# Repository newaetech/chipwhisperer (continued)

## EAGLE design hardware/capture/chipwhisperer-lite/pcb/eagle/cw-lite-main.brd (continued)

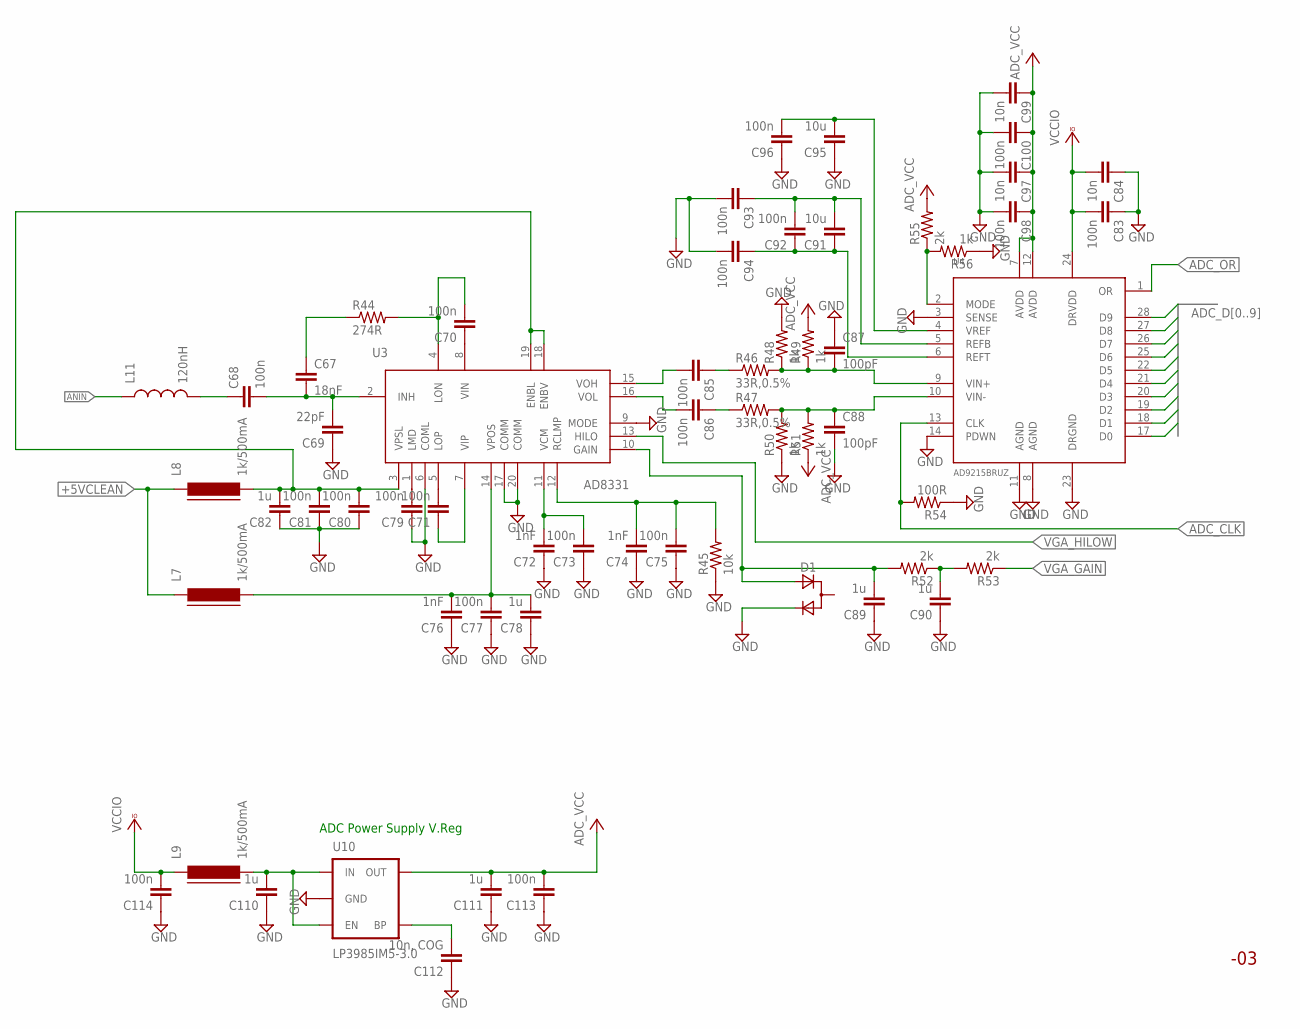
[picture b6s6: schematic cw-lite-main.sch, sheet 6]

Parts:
C67: 18nF; 0603C
C68, C85, C86: 100n; 0603C
C69: 22pF; 0603C
C70, C71, C73, C75, C77, C79, C80, C81, C83, C92, C93, C94, C96, C98, C100, C113, C114: 100n; 0402C
C72, C74, C76: 1nF; 0402C
C78, C82, C89, C90, C110, C111: 1u; 0603C
C84, C97, C99: 10n; 0402C
C87, C88: 100pF; 0603C
C91, C95: 10u; 0603C
C112: 10n, COG; 0402C
D1: D_ACACSOT23; SOT-23; MPN BAV99-7F
L7, L8, L9: 1k/500mA; FB603
L11: 120nH; 0603
R44: 274R; 0603R
R45: 10k; 0603R
R46, R47: 33R,0.5%; 0603R
R48, R49, R50, R51: 1k; 0402R
R52, R53, R55: 2k; 0603R
R54: 100R; 0603R
R56: 1k; 0603R
U3: AD8331; QSOP20; MPN AD8331ARQZ
U4: AD9215BRUZ; TSSOP28; MPN AD9215BRUZ-105
U10: LP3985IM5-3.0; SOT23-5; MPN LP3985IM5X-3.0/NOPB

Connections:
+5VCLEAN: L7.1, L8.1; also elsewhere on the board
ADC_CLK: R54.2, U4.13 (CLK); also elsewhere on the board
ADC_D0: U4.17 (D0); also elsewhere on the board
ADC_D1: U4.18 (D1); also elsewhere on the board
ADC_D2: U4.19 (D2); also elsewhere on the board
ADC_D3: U4.20 (D3); also elsewhere on the board
ADC_D4: U4.21 (D4); also elsewhere on the board
ADC_D5: U4.22 (D5); also elsewhere on the board
ADC_D6: U4.25 (D6); also elsewhere on the board
ADC_D7: U4.26 (D7); also elsewhere on the board
ADC_D8: U4.27 (D8); also elsewhere on the board
ADC_D9: U4.28 (D9); also elsewhere on the board
ADC_OR: U4.1 (OR); also elsewhere on the board
ADC_VCC: C97.1, C98.1, C99.1, C100.1, C111.2, C113.2, R49.2, R51.1, R55.2, U4.7 (AVDD), U4.12 (AVDD), U10.5 (OUT)
ANIN: L11.1; also elsewhere on the board
GND: C69.1, C72.1, C73.1, C74.1, C75.1, C76.1, C77.1, C78.1, C79.1, C80.1, C81.1, C82.1, C83.1, C84.1, C87.1, C88.2, C89.1, C90.1, C93.2, C94.2, C95.1, C96.1, C97.2, C98.2, C99.2, C100.2, C110.1, C111.1, C112.1, C113.1, C114.1, D1.2 (C), R45.1, R48.2, R50.1, R54.1, R56.1, U3.6 (COML), U3.9 (MODE), U3.17 (COMM), U3.20 (COMM), U4.3 (SENSE), U4.8 (AGND), U4.11 (AGND), U4.14 (PDWN), U4.23 (DRGND), U10.2 (GND); also elsewhere on the board
unnamed: C68.1, L11.2
unnamed: C110.2, L9.2, U10.1 (IN), U10.3 (EN)
unnamed: C112.2, U10.4 (BP)
unnamed: C67.2, C68.2, C69.2, U3.2 (INH)
unnamed: C70.2, R44.2, U3.4 (LON)
unnamed: C67.1, R44.1
unnamed: C70.1, U3.8 (VIN)
unnamed: C71.2, U3.5 (LOP)
unnamed: C74.2, C75.2, R45.2, U3.12 (RCLMP)
unnamed: C72.2, C73.2, U3.11 (VCM)
unnamed: C79.2, U3.1 (LMD)
unnamed: C89.2, D1.3 (A), R52.2, U3.10 (GAIN)
unnamed: C80.2, C81.2, C82.2, L8.2, U3.3 (VPSL), U3.18 (ENBV), U3.19 (ENBL)
unnamed: C71.1, U3.7 (VIP)
unnamed: C76.2, C77.2, C78.2, L7.2, U3.14 (VPOS)
unnamed: C87.2, R46.2, R48.1, R49.1, U4.9 (VIN+)
unnamed: C88.1, R47.2, R50.2, R51.2, U4.10 (VIN-)
unnamed: C85.2, U3.15 (VOH)
unnamed: C86.2, U3.16 (VOL)
unnamed: C85.1, R46.1
unnamed: C86.1, R47.1
unnamed: C91.2, C92.2, C93.1, U4.5 (REFB)
unnamed: C91.1, C92.1, C94.1, U4.6 (REFT)
unnamed: C90.2, R52.1, R53.2
unnamed: C95.2, C96.2, U4.4 (VREF)
unnamed: R55.1, R56.2, U4.2 (MODE)
VCCIO: C83.2, C84.2, C114.2, L9.1, U4.24 (DRVDD); also elsewhere on the board
VGA_GAIN: R53.1; also elsewhere on the board
VGA_HILOW: U3.13 (HILO); also elsewhere on the board

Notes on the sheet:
ADC Power Supply V.Reg

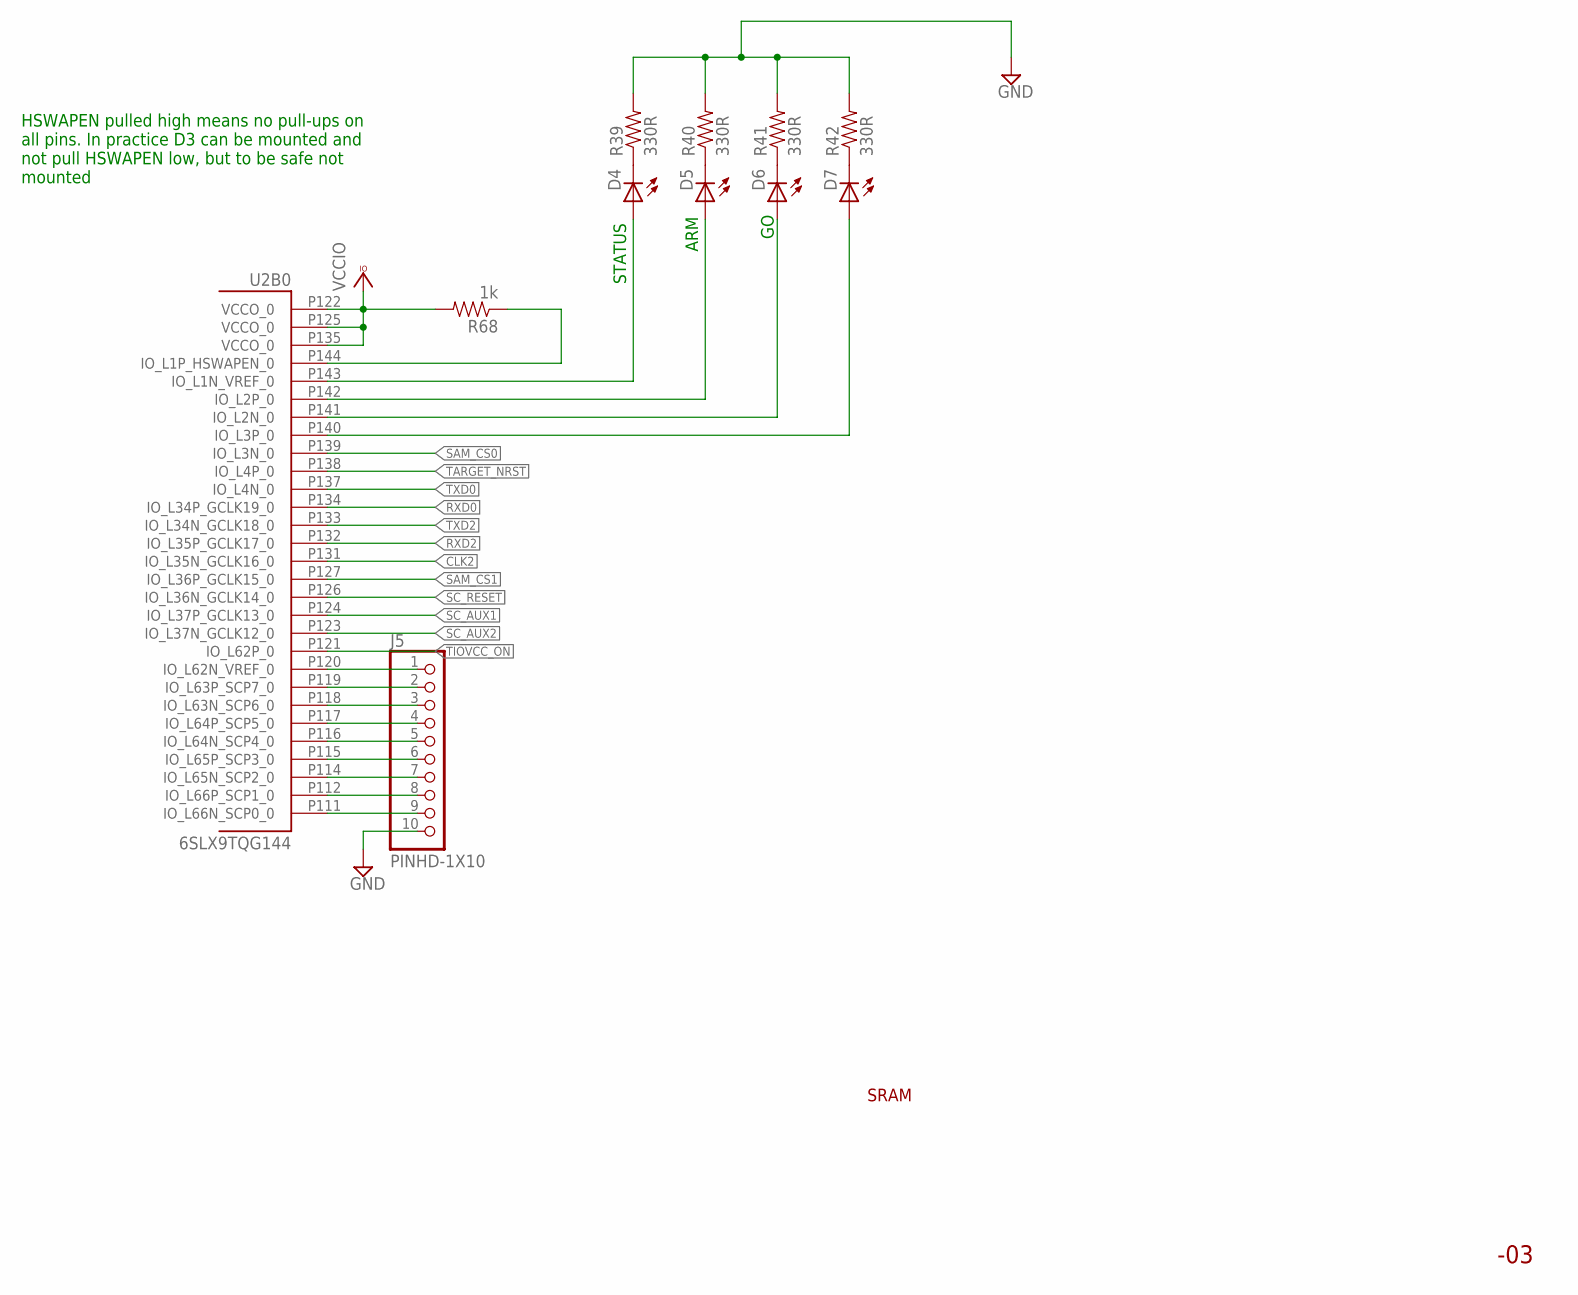
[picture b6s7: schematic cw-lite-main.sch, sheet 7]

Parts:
D4, D5, D6, D7: LED0603; LED-0603
J5: PINHD-1X10; 1X10-BIG
R39, R40, R41, R42: 330R; 0402R
R68: 1k; 0402R
U2: 6SLX9TQG144; TQ144; MPN XC6SLX9-3TQG144C

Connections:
!TIOVCC_ON: U2.P121 (IO_L62P_0); also elsewhere on the board
CLK2: U2.P131 (IO_L35N_GCLK16_0); also elsewhere on the board
GND: J5.10, R39.2, R40.2, R41.2, R42.2; also elsewhere on the board
LED_ARMED: D6.A, U2.P141 (IO_L2N_0)
LED_CAPTURE: D5.A, U2.P142 (IO_L2P_0)
LED_STATUS: R68.1, U2.P144 (IO_L1P_HSWAPEN_0)
LED_TCLOCK: D7.A, U2.P140 (IO_L3P_0)
LED_USBACT: D4.A, U2.P143 (IO_L1N_VREF_0)
unnamed: J5.1, U2.P120 (IO_L62N_VREF_0)
unnamed: J5.2, U2.P119 (IO_L63P_SCP7_0)
unnamed: J5.3, U2.P118 (IO_L63N_SCP6_0)
unnamed: J5.4, U2.P117 (IO_L64P_SCP5_0)
unnamed: J5.5, U2.P116 (IO_L64N_SCP4_0)
unnamed: J5.6, U2.P115 (IO_L65P_SCP3_0)
unnamed: J5.7, U2.P114 (IO_L65N_SCP2_0)
unnamed: J5.8, U2.P112 (IO_L66P_SCP1_0)
unnamed: J5.9, U2.P111 (IO_L66N_SCP0_0)
unnamed: D4.C, R39.1
unnamed: D5.C, R40.1
unnamed: D6.C, R41.1
unnamed: D7.C, R42.1
RXD0: U2.P134 (IO_L34P_GCLK19_0); also elsewhere on the board
RXD2: U2.P132 (IO_L35P_GCLK17_0); also elsewhere on the board
SAM_CS0: U2.P139 (IO_L3N_0); also elsewhere on the board
SAM_CS1: U2.P127 (IO_L36P_GCLK15_0); also elsewhere on the board
SC_AUX1: U2.P124 (IO_L37P_GCLK13_0); also elsewhere on the board
SC_AUX2: U2.P123 (IO_L37N_GCLK12_0); also elsewhere on the board
SC_RESET: U2.P126 (IO_L36N_GCLK14_0); also elsewhere on the board
TARGET_NRST: U2.P138 (IO_L4P_0); also elsewhere on the board
TXD0: U2.P137 (IO_L4N_0); also elsewhere on the board
TXD2: U2.P133 (IO_L34N_GCLK18_0); also elsewhere on the board
VCCIO: R68.2, U2.P122 (VCCO_0), U2.P125 (VCCO_0), U2.P135 (VCCO_0); also elsewhere on the board

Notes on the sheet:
SRAM
HSWAPEN pulled high means no pull-ups on all pins. In practice D3 can be mounted and not pull HSWAPEN low, but to be safe not mounted
STATUS
ARM

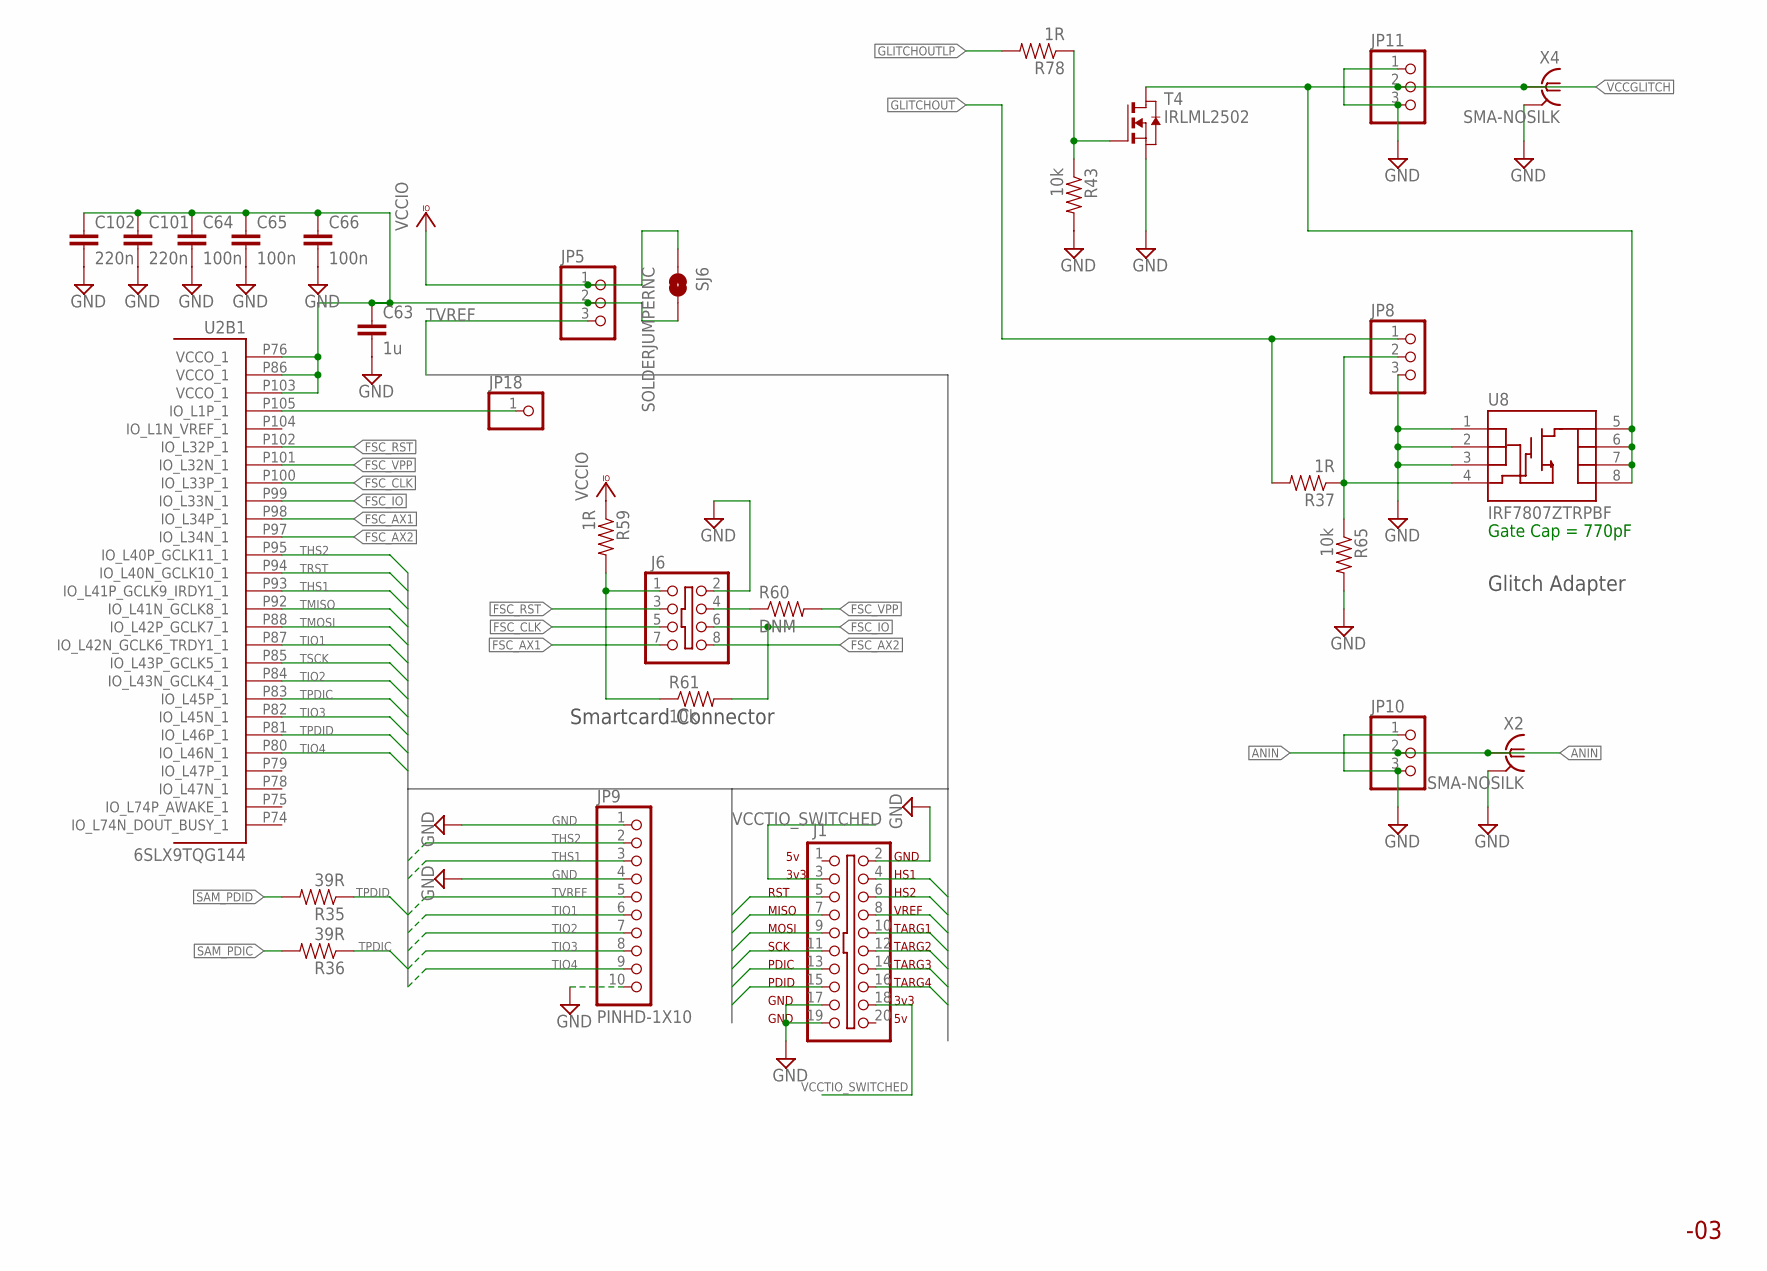
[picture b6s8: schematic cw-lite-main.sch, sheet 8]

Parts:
C63: 1u; 0603C
C64, C65, C66: 100n; 0402C
C101, C102: 220n; 0402C
J1: SHROUD_2X10-SHROUDED; PINSHRD_PTH_2X10
J6: SHROUD_2X4SHROUD; PINSHRD_PTH_2X04
JP5, JP8, JP10, JP11: PINHD-1X3; 1X03
JP9: PINHD-1X10; 1X10-BIG
JP18: PINHD-1X1; 1X01
R35, R36: 39R; 0603R
R37, R59, R78: 1R; 0603R
R43, R61, R65: 10k; 0603R
R60: DNM; 0603R
SJ6: SOLDERJUMPERNC; SJ_2S
T4: IRLML2502; SOT-23; MPN IRLML2502TRPBF
U2: 6SLX9TQG144; TQ144; MPN XC6SLX9-3TQG144C
U8: IRF7807ZTRPBF; SO08
X2, X4: SMA-NOSILK; J502-ND-142-0711-821/826-NOSILK

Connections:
ANIN: JP10.2, X2.1; also elsewhere on the board
FSC_AX1: J6.7, U2.P98 (IO_L34P_1)
FSC_AX2: J6.8, U2.P97 (IO_L34N_1)
FSC_CLK: J6.5, U2.P100 (IO_L33P_1)
FSC_IO: J6.6, R61.2, U2.P99 (IO_L33N_1)
FSC_RST: J6.3, U2.P102 (IO_L32P_1)
FSC_VPP: R60.2, U2.P101 (IO_L32N_1)
GLITCHOUT: JP8.1, R37.2; also elsewhere on the board
GLITCHOUTLP: R78.2; also elsewhere on the board
GND: C63.2, C64.2, C65.2, C66.2, C101.2, C102.2, J1.2, J1.17, J1.19, J6.2, JP8.3, JP9.1, JP9.4, JP9.10, JP10.1, JP10.3, JP11.1, JP11.3, R43.2, R65.2, T4.2 (S), U8.1 (S), U8.2 (S), U8.3 (S), X2.G@1 (2), X2.G@2 (2), X2.G@3 (2), X2.G@4 (2), X4.G@1 (2), X4.G@2 (2), X4.G@3 (2), X4.G@4 (2); also elsewhere on the board
unnamed: JP8.2, R37.1, R65.1, U8.4 (G)
unnamed: JP18.1, U2.P105 (IO_L1P_1)
unnamed: R43.1, R78.1, T4.3 (G)
unnamed: J6.1, R59.2, R61.1
unnamed: J6.4, R60.1
SAM_PDIC: R36.2; also elsewhere on the board
SAM_PDID: R35.2; also elsewhere on the board
TARGET_VCCIO: C63.1, C64.1, C65.1, C66.1, C101.1, C102.1, JP5.2, SJ6.2, U2.P76 (VCCO_1), U2.P86 (VCCO_1), U2.P103 (VCCO_1)
THS1: J1.4, JP9.3, U2.P93 (IO_L41P_GCLK9_IRDY1_1); also elsewhere on the board
THS2: J1.6, JP9.2, U2.P95 (IO_L40P_GCLK11_1); also elsewhere on the board
TIO1: J1.10, JP9.6, U2.P87 (IO_L42N_GCLK6_TRDY1_1); also elsewhere on the board
TIO2: J1.12, JP9.7, U2.P84 (IO_L43N_GCLK4_1); also elsewhere on the board
TIO3: J1.14, JP9.8, U2.P82 (IO_L45N_1); also elsewhere on the board
TIO4: J1.16, JP9.9, U2.P80 (IO_L46N_1); also elsewhere on the board
TMISO: J1.7, U2.P92 (IO_L41N_GCLK8_1); also elsewhere on the board
TMOSI: J1.9, U2.P88 (IO_L42P_GCLK7_1); also elsewhere on the board
TPDIC: J1.13, R36.1, U2.P83 (IO_L45P_1); also elsewhere on the board
TPDID: J1.15, R35.1, U2.P81 (IO_L46P_1); also elsewhere on the board
TRST: J1.5, U2.P94 (IO_L40N_GCLK10_1); also elsewhere on the board
TSCK: J1.11, U2.P85 (IO_L43P_GCLK5_1); also elsewhere on the board
TVREF: J1.8, JP5.3, JP9.5; also elsewhere on the board
VCCGLITCH: JP11.2, T4.1 (D), U8.5 (D), U8.6 (D), U8.7 (D), U8.8 (D), X4.1; also elsewhere on the board
VCCIO: JP5.1, R59.1, SJ6.1; also elsewhere on the board
VCCTIO_SWITCHED: J1.3, J1.18; also elsewhere on the board

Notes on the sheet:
HS1
HS2
VREF
TARG1
TARG2
TARG3
TARG4
3v3
RST
MISO
MOSI
SCK
PDIC
PDID
GND
Glitch Adapter
Smartcard Connector
Gate Cap = 770pF

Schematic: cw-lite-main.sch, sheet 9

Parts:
C37: 47u; 0805
C103: 10u; 0603C
C104: 10n; 0603C
C105, C107: 1u; 0603C
C106, C108, C109: 100n; 0603C
C115, C116, C121: DNM; 0603C
C118, C119, C120: CAP0603-CAP; 0603C
J2: SHROUD_2X10-SHROUDED; PINSHRD_PTH_2X10
J9: MICRO-USB-5P-ZX62D-B-5P8; B-SMD-5P-TH
JP6, JP7, JP12: PINHD-1X2; 1X02
JP13: PINHD-1X9; 1X09-BIG
JP14, JP15, JP16, JP17: PINHD-1X1; 1X01
L10: 1k/500mA; FB603
LED9, LED10: LED-0603; LED-603
Q2: CRYSTALHC49U-V; HC49U-V
R13: 10k; 0603R
R66, R76: 49R9; 0805
R67, R72: 100R; 0603R
R73: DNM; 0603R
R74, R75: 1k; 0603R
SJ2: SOLDERJUMPER_2WAYPASTE2&3; SJ_3_PASTE2&3
SJ3, SJ4, SJ5, SJ7: SOLDERJUMPERNC; SJ_2S
U11: V_REG_MIC2920; SOT223
U12: XMEGA128A4U; TQFP44; MPN ATXMEGA128A4U-AU
X3, X5: SMA-NOSILK; J502-ND-142-0711-821/826-NOSILK

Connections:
ANIN: JP7.2, SJ4.2, X3.1; also elsewhere on the board
GND: C37.2, C103.2, C104.2, C105.2, C106.2, C107.2, C108.2, C109.1, C115.2, C116.1, C118.1, C119.1, C120.1, C121.1, J2.2, J2.17, J2.19, J9.5 (GND), JP13.9, U11.2 (GND), U12.8 (GND), U12.18 (GND1), U12.30 (GND2), U12.38 (GND3), X3.G@1 (2), X3.G@2 (2), X3.G@3 (2), X3.G@4 (2), X5.G@1 (2), X5.G@2 (2), X5.G@3 (2), X5.G@4 (2); also elsewhere on the board
unnamed: C118.2, J9.E1 (SHIELD), J9.E2 (SHIELD), J9.P$1 (SHIELD), J9.P$2 (SHIELD), J9.P$3 (SHIELD), J9.P$4 (SHIELD)
unnamed: C107.1, C108.1, C109.2, JP12.1, R66.2, SJ3.2, U12.39 (AVCC)
unnamed: C121.2, JP6.1, JP7.1, R66.1, SJ4.1, SJ5.1, U12.9 (VCC), U12.19 (VCC1), U12.31 (VCC2)
unnamed: C119.2, J9.1 (VCC), U11.1 (IN)
unnamed: C120.2, SJ2.1, U11.3 (OUT)
unnamed: LED9.A, R74.1
unnamed: LED10.A, R75.1
unnamed: LED9.C, U12.1 (PA5)
unnamed: LED10.C, U12.2 (PA6)
unnamed: JP13.1, U12.25 (PD5)
unnamed: JP13.2, U12.24 (PD4)
unnamed: JP13.3, U12.23 (PD3)
unnamed: JP13.4, U12.22 (PD2)
unnamed: JP13.5, U12.21 (PD1)
unnamed: C115.1, Q2.2, R72.1, U12.37 (PR1(XT1))
unnamed: C116.2, Q2.1, R73.1, U12.36 (PR0(XT2))
unnamed: R67.2, U12.7 (PB3)
unnamed: JP13.6, U12.20 (PD0)
unnamed: L10.2, R76.2
unnamed: C37.1, C105.1, C106.1, JP12.2, R76.1, SJ3.1
THS1: J2.4, R67.1; also elsewhere on the board
THS2: J2.6, R72.2, R73.2; also elsewhere on the board
TIO1: J2.10, JP16.1, U12.13 (PC3); also elsewhere on the board
TIO2: J2.12, JP17.1, U12.12 (PC2); also elsewhere on the board
TIO3: J2.14, JP14.1, U12.41 (PA1); also elsewhere on the board
TIO4: J2.16, JP15.1, U12.40 (PA0); also elsewhere on the board
TMISO: J2.7; also elsewhere on the board
TMOSI: J2.9; also elsewhere on the board
TPC6: JP13.8, U12.16 (PC6)
TPC7: JP13.7, U12.17 (PC7)
TPDIC: J2.13, R13.2, U12.35 (!RESET!/PDI_CLK); also elsewhere on the board
TPDID: J2.15, U12.34 (PDI_DATA); also elsewhere on the board
TRST: J2.5; also elsewhere on the board
TSCK: J2.11; also elsewhere on the board
TUSB_N: J9.2 (DM), U12.26 (PD6)
TUSB_P: J9.3 (DP), U12.27 (PD7)
TVREF: J2.8, SJ7.2; also elsewhere on the board
VCCGLITCH: JP6.2, SJ5.2, X5.1; also elsewhere on the board
VCCTIO_SWITCHED: J2.3, J2.18, SJ2.3; also elsewhere on the board
VCC_TARG: C103.1, C104.1, L10.1, R13.1, R74.2, R75.2, SJ2.2, SJ7.1

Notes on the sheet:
Breakaway Section of PCB
Might be XMEGA128D3 instead?

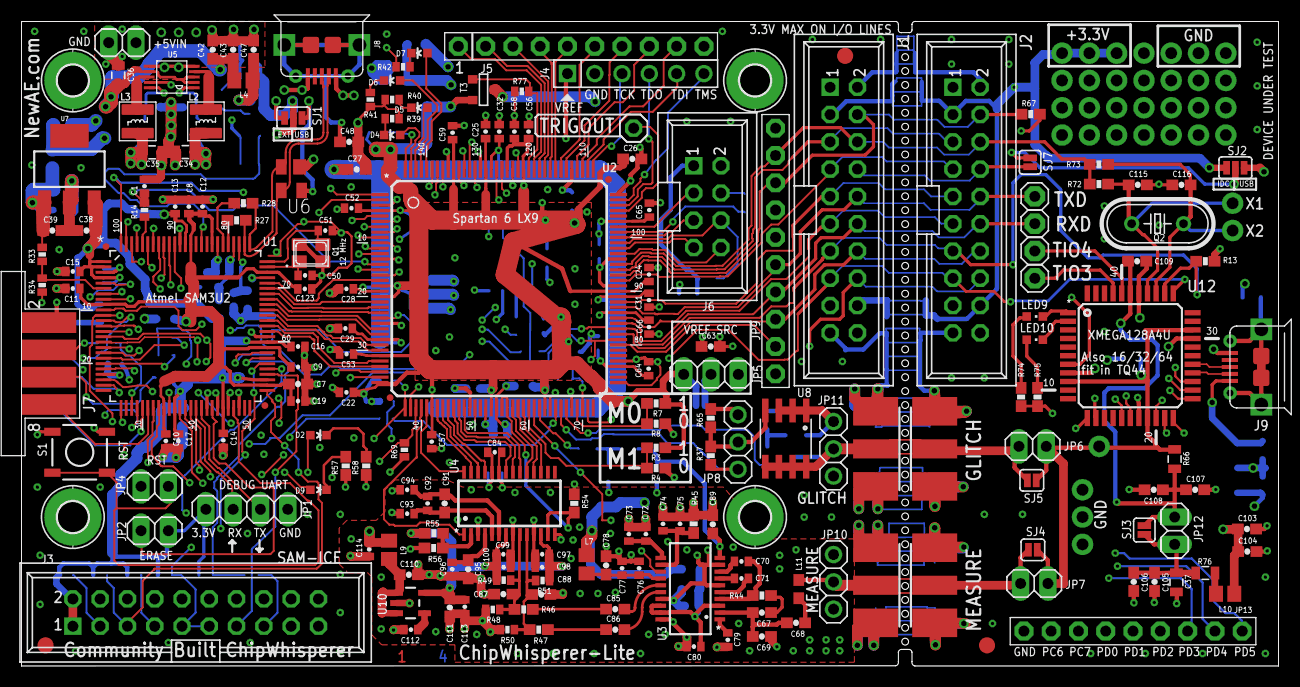
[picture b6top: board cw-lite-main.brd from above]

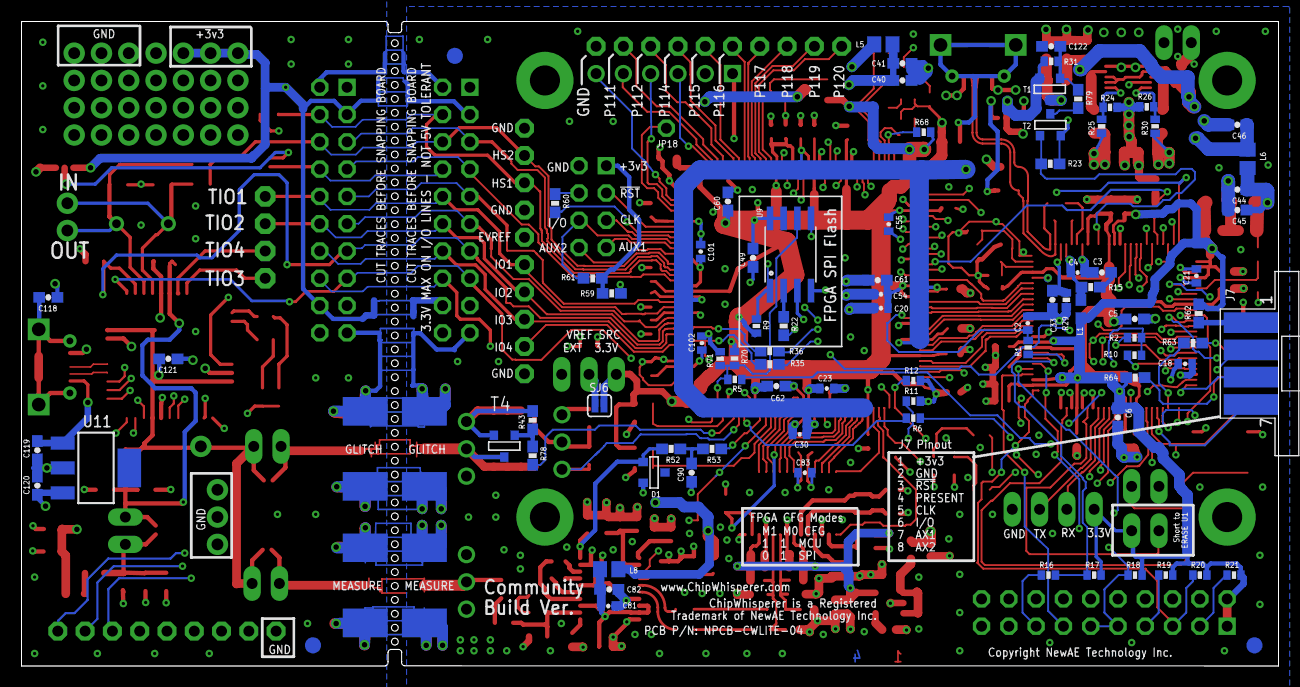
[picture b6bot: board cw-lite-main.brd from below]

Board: 4 copper layers, 117.0 x 60.0 mm, 290 parts (86 on the bottom side), 223 nets.

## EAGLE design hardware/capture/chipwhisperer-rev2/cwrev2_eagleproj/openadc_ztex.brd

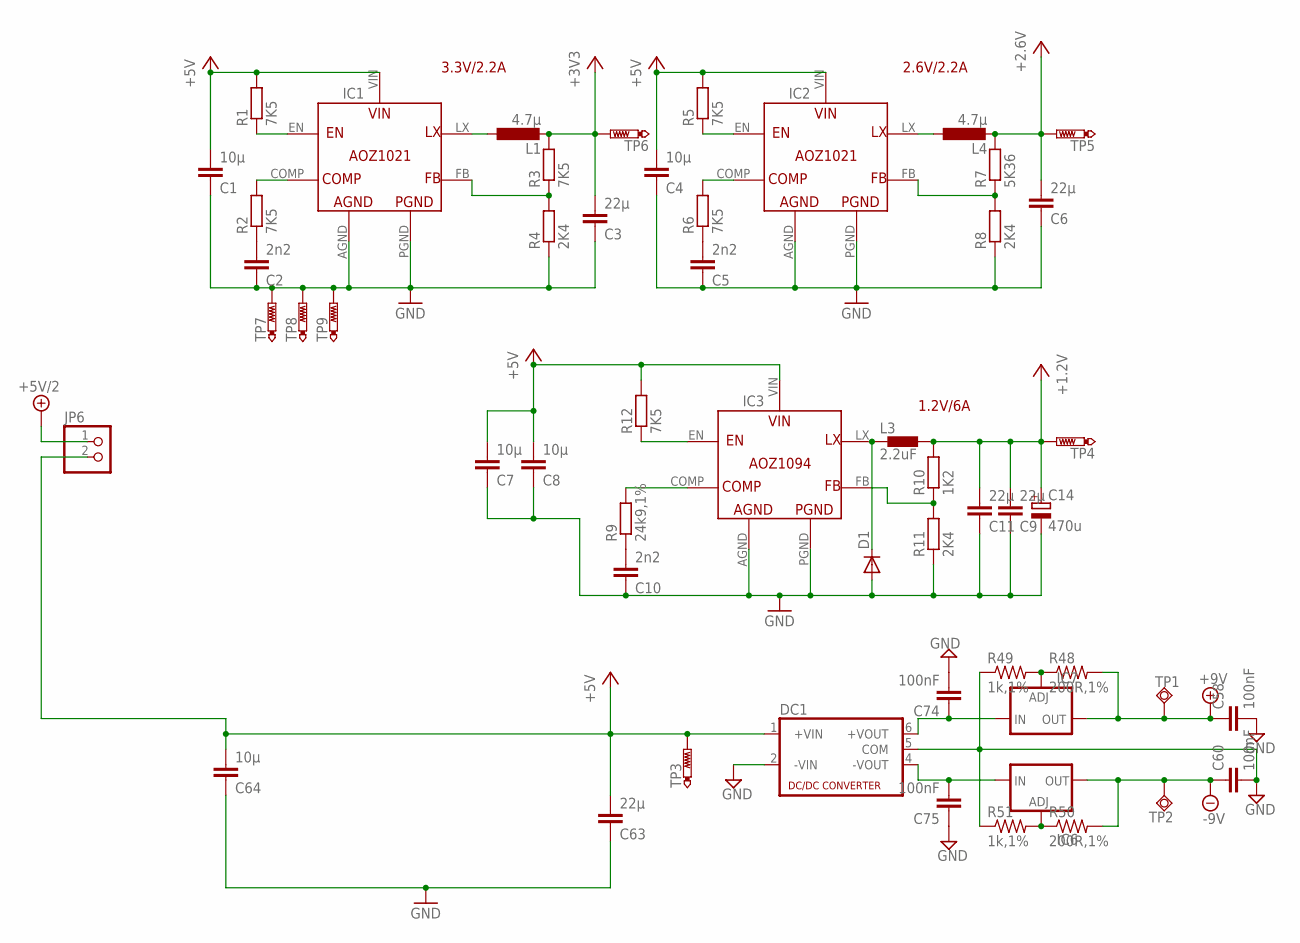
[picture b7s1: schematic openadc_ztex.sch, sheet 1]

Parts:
C1, C4, C7, C8, C64: 10µ; C1206
C2, C5, C10: 2n2; C0805K
C3, C6, C9, C11, C63: 22µ; C0805K
C14: 470u; E2,5-6
C58, C60, C74, C75: 100nF; C0603
D1: DIODE-MELF-MLL41; MELF-MLL41
DC1: NMA
IC1, IC2: AOZ1021
IC3: AOZ1094; AOZ1094.PAC
IC6: LM337L; 337L
IC7: LM317L; 317L
JP6: PINHD-1X2; 1X02
L1, L4: 4.7µ; NR60; DIGIKEY# 587-2100-1-ND
L3: 2.2uF; DR1030MOD.PAC; MPN CDRH104RNP-2R5NC
R1, R2, R3, R5, R6, R12: 7K5; R0805K
R4, R8, R11: 2K4; R0805K
R7: 5K36; R0805K
R9: 24k9,1%; R0805K
R10: 1K2; R0805K
R48, R50: 200R,1%; R0603
R49, R51: 1k,1%; R0603
TP1, TP2: TPSQPAD1-13; P1-13
TP3, TP4, TP5, TP6, TP7, TP8, TP9: PTR1PAD1-13; P1-13

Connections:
+1.2V: C9.2, C11.2, C14.+, L3.2, R10.2, TP4.TP; also elsewhere on the board
+2.6V: C6.2, L4.P$2 (2), R7.2, TP5.TP; also elsewhere on the board
+3V3: C3.2, L1.P$2 (2), R3.2, TP6.TP; also elsewhere on the board
+5V: C1.2, C4.2, C7.2, C8.2, C63.2, C64.2, DC1.1 (+VIN), IC1.VIN, IC2.VIN, IC3.VIN, JP6.2, R1.2, R5.2, R12.2, TP3.TP; also elsewhere on the board
+5V/2: JP6.1; also elsewhere on the board
+9V: C58.1, IC7.2 (OUT), R48.2, TP1.TP; also elsewhere on the board
-9V: C60.1, IC6.OUT, R50.2, TP2.TP; also elsewhere on the board
GND: C1.1, C2.1, C3.1, C4.1, C5.1, C6.1, C7.1, C8.1, C9.1, C10.1, C11.1, C14.-, C58.2, C60.2, C63.1, C64.1, C74.2, C75.1, D1.A, DC1.2 (-VIN), DC1.5 (COM), IC1.AGND, IC1.PGND, IC2.AGND, IC2.PGND, IC3.AGND, IC3.PGND, R4.1, R8.1, R11.1, R49.1, R51.1, TP7.TP, TP8.TP, TP9.TP; also elsewhere on the board
unnamed: IC3.EN, R12.1
unnamed: IC1.LX, L1.P$1 (1)
unnamed: IC1.FB, R3.1, R4.2
unnamed: D1.C, IC3.LX, L3.1
unnamed: IC1.EN, R1.1
unnamed: IC3.FB, R10.1, R11.2
unnamed: C2.2, R2.1
unnamed: IC1.COMP, R2.2
unnamed: C10.2, R9.1
unnamed: IC3.COMP, R9.2
unnamed: IC2.LX, L4.P$1 (1)
unnamed: IC2.FB, R7.1, R8.2
unnamed: IC2.EN, R5.1
unnamed: C5.2, R6.1
unnamed: IC2.COMP, R6.2
unnamed: C74.1, DC1.6 (+VOUT), IC7.3 (IN)
unnamed: C75.2, DC1.4 (-VOUT), IC6.IN
unnamed: IC6.ADJ, R50.1, R51.2
unnamed: IC7.1 (ADJ), R48.1, R49.2

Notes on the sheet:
3.3V/2.2A
2.6V/2.2A
1.2V/6A

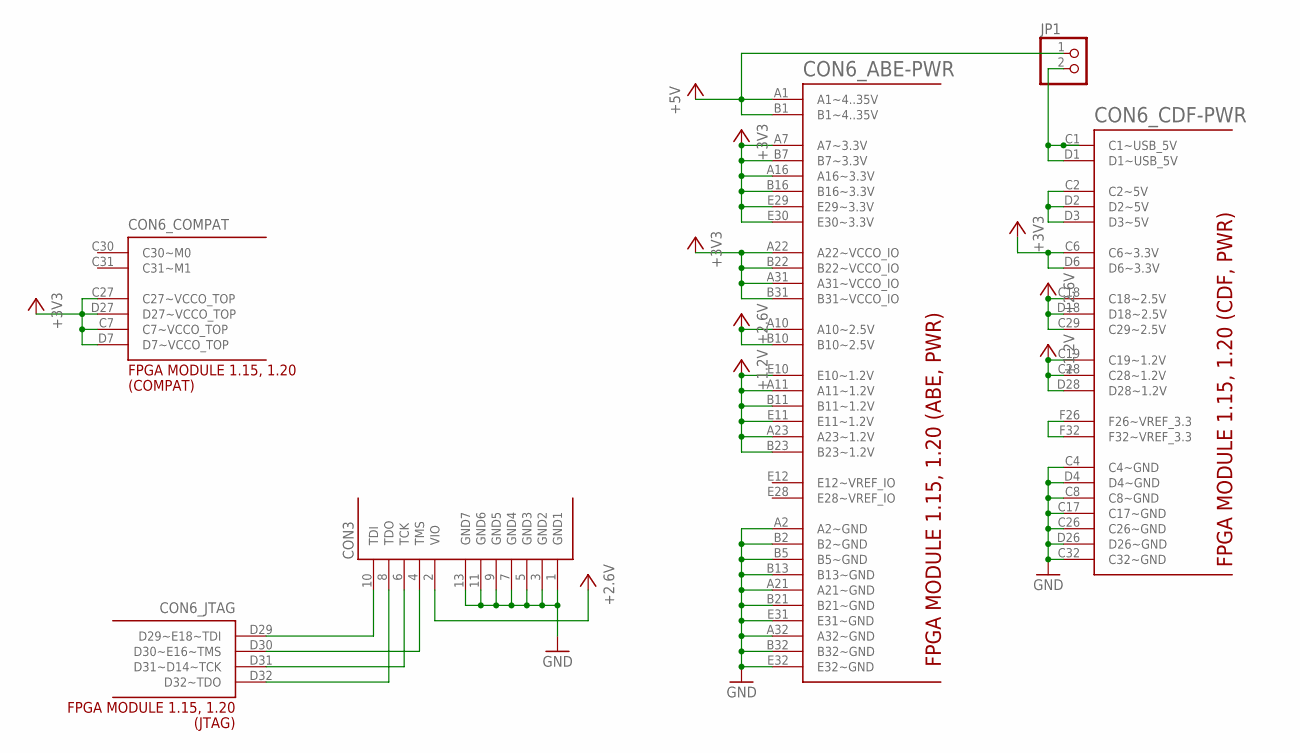
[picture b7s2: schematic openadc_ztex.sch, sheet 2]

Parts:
CON3: JTAG
CON6: USB-FPGA1.15
JP1: PINHD-1X2; 1X02

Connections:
+1.2V: CON6.A11 (A11~1.2V), CON6.A23 (A23~1.2V), CON6.B11 (B11~1.2V), CON6.B23 (B23~1.2V), CON6.C19 (C19~1.2V), CON6.C28 (C28~1.2V), CON6.D28 (D28~1.2V), CON6.E10 (E10~1.2V), CON6.E11 (E11~1.2V); also elsewhere on the board
+2.6V: CON3.2 (VIO), CON6.A10 (A10~2.5V), CON6.B10 (B10~2.5V), CON6.C18 (C18~2.5V), CON6.C29 (C29~2.5V), CON6.D18 (D18~2.5V); also elsewhere on the board
+3V3: CON6.A7 (A7~3.3V), CON6.A16 (A16~3.3V), CON6.A22 (A22~VCCO_IO), CON6.A31 (A31~VCCO_IO), CON6.B7 (B7~3.3V), CON6.B16 (B16~3.3V), CON6.B22 (B22~VCCO_IO), CON6.B31 (B31~VCCO_IO), CON6.C6 (C6~3.3V), CON6.C7 (C7~VCCO_TOP), CON6.C27 (C27~VCCO_TOP), CON6.D6 (D6~3.3V), CON6.D7 (D7~VCCO_TOP), CON6.D27 (D27~VCCO_TOP), CON6.E29 (E29~3.3V), CON6.E30 (E30~3.3V); also elsewhere on the board
+5V: CON6.A1 (A1~4..35V), CON6.B1 (B1~4..35V), JP1.1; also elsewhere on the board
GND: CON3.1 (GND1), CON3.3 (GND2), CON3.5 (GND3), CON3.7 (GND4), CON3.9 (GND5), CON3.11 (GND6), CON3.13 (GND7), CON6.A2 (A2~GND), CON6.A21 (A21~GND), CON6.A32 (A32~GND), CON6.B2 (B2~GND), CON6.B5 (B5~GND), CON6.B13 (B13~GND), CON6.B21 (B21~GND), CON6.B32 (B32~GND), CON6.C4 (C4~GND), CON6.C8 (C8~GND), CON6.C17 (C17~GND), CON6.C26 (C26~GND), CON6.C32 (C32~GND), CON6.D4 (D4~GND), CON6.D26 (D26~GND), CON6.E31 (E31~GND), CON6.E32 (E32~GND); also elsewhere on the board
unnamed: CON6.C1 (C1~USB_5V), CON6.D1 (D1~USB_5V), JP1.2
unnamed: CON6.C2 (C2~5V), CON6.D2 (D2~5V), CON6.D3 (D3~5V)
unnamed: CON6.F26 (F26~VREF_3.3), CON6.F32 (F32~VREF_3.3)
unnamed: CON3.8 (TDO), CON6.D32 (D32~TDO)
unnamed: CON3.10 (TDI), CON6.D29 (D29~E18~TDI)
unnamed: CON3.6 (TCK), CON6.D31 (D31~D14~TCK)
unnamed: CON3.4 (TMS), CON6.D30 (D30~E16~TMS)

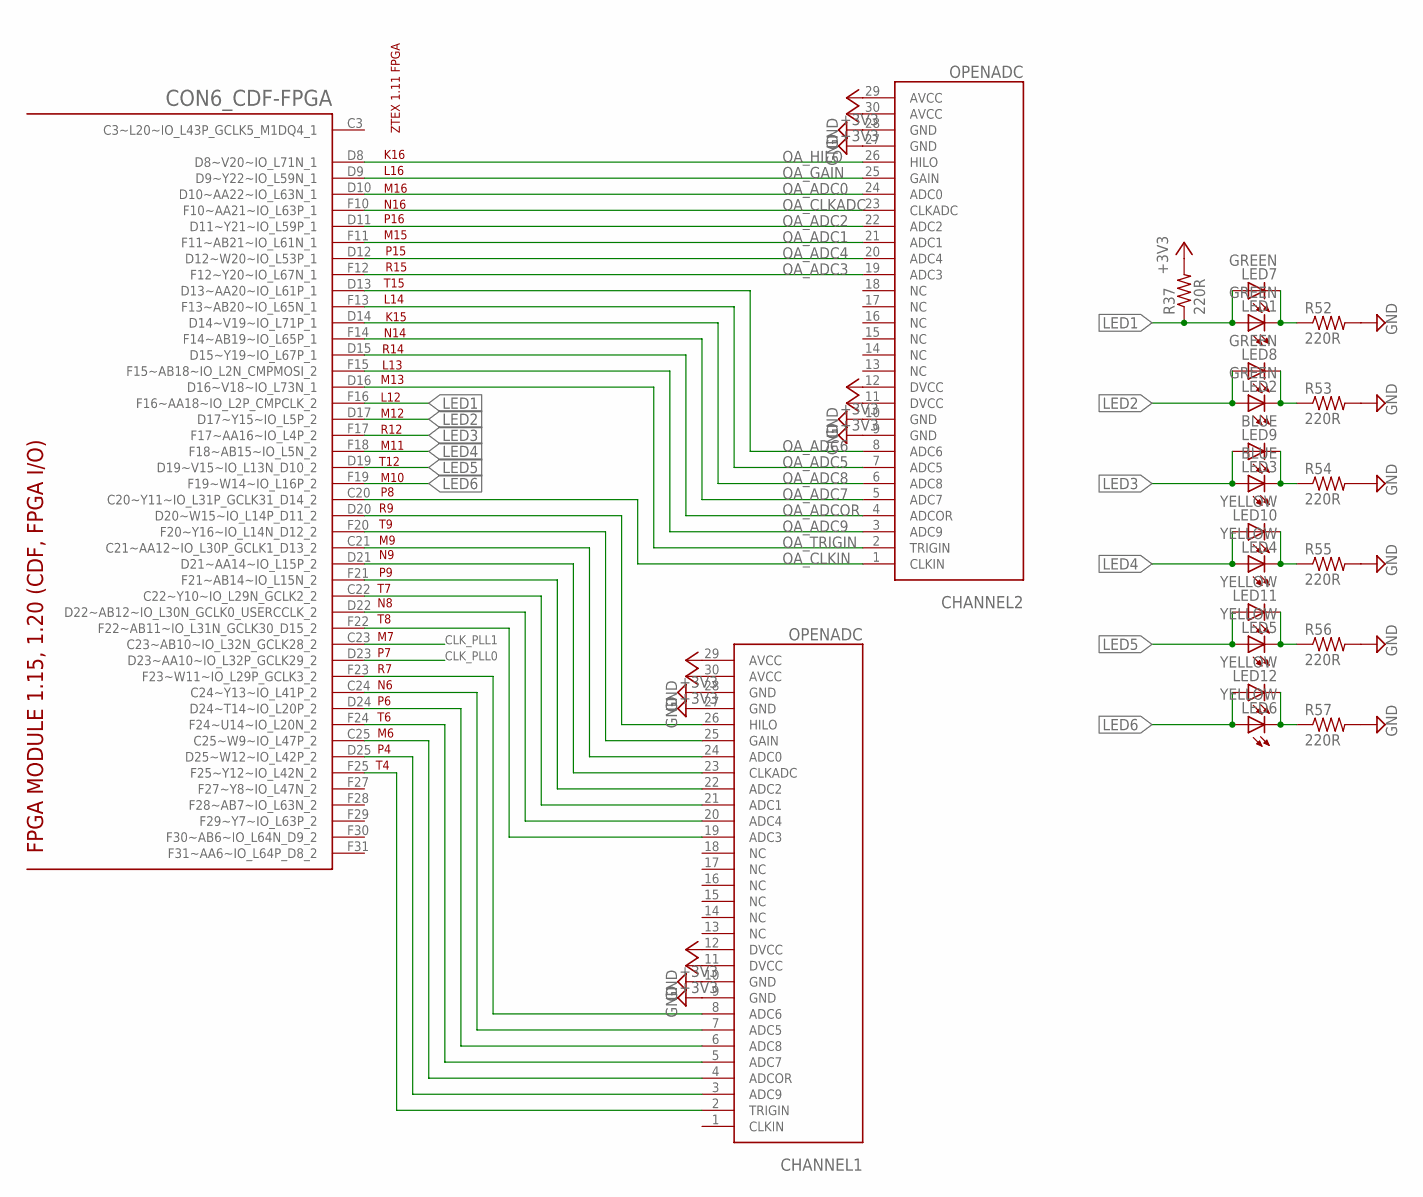
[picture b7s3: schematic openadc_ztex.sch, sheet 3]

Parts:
CHANNEL1, CHANNEL2: OPENADC; OPENADCREV1
CON6: USB-FPGA1.15
LED1, LED2, LED7, LED8: GREEN; LED-805
LED3, LED9: BLUE; LED-805
LED4, LED5, LED6, LED10, LED11, LED12: YELLOW; LED-805
R37, R52, R53, R54, R55, R56, R57: 220R; R0603

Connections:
+3V3: CHANNEL1.11 (DVCC), CHANNEL1.12 (DVCC), CHANNEL1.29 (AVCC), CHANNEL1.30 (AVCC), CHANNEL2.11 (DVCC), CHANNEL2.12 (DVCC), CHANNEL2.29 (AVCC), CHANNEL2.30 (AVCC), R37.2; also elsewhere on the board
CLK_PLL0: CON6.D23 (D23~AA10~IO_L32P_GCLK29_2); also elsewhere on the board
CLK_PLL1: CON6.C23 (C23~AB10~IO_L32N_GCLK28_2); also elsewhere on the board
GND: CHANNEL1.9 (GND), CHANNEL1.10 (GND), CHANNEL1.27 (GND), CHANNEL1.28 (GND), CHANNEL2.9 (GND), CHANNEL2.10 (GND), CHANNEL2.27 (GND), CHANNEL2.28 (GND), R52.2, R53.2, R54.2, R55.2, R56.2, R57.2; also elsewhere on the board
LED1: CON6.F16 (F16~AA18~IO_L2P_CMPCLK_2), LED1.A, LED7.A, R37.1
LED2: CON6.D17 (D17~Y15~IO_L5P_2), LED2.A, LED8.A
LED3: CON6.F17 (F17~AA16~IO_L4P_2), LED3.A, LED9.A
LED4: CON6.F18 (F18~AB15~IO_L5N_2), LED4.A, LED10.A
LED5: CON6.D19 (D19~V15~IO_L13N_D10_2), LED5.A, LED11.A
LED6: CON6.F19 (F19~W14~IO_L16P_2), LED6.A, LED12.A
unnamed: CHANNEL1.21 (ADC1), CON6.C22 (C22~Y10~IO_L29N_GCLK2_2)
unnamed: CHANNEL1.26 (HILO), CON6.D20 (D20~W15~IO_L14P_D11_2)
unnamed: CHANNEL1.20 (ADC4), CON6.D22 (D22~AB12~IO_L30N_GCLK0_USERCCLK_2)
unnamed: CHANNEL1.25 (GAIN), CON6.F20 (F20~Y16~IO_L14N_D12_2)
unnamed: CHANNEL1.24 (ADC0), CON6.C21 (C21~AA12~IO_L30P_GCLK1_D13_2)
unnamed: CHANNEL1.23 (CLKADC), CON6.D21 (D21~AA14~IO_L15P_2)
unnamed: CHANNEL1.22 (ADC2), CON6.F21 (F21~AB14~IO_L15N_2)
unnamed: CHANNEL1.19 (ADC3), CON6.F22 (F22~AB11~IO_L31N_GCLK30_D15_2)
unnamed: CHANNEL1.8 (ADC6), CON6.F23 (F23~W11~IO_L29P_GCLK3_2)
unnamed: CHANNEL1.7 (ADC5), CON6.C24 (C24~Y13~IO_L41P_2)
unnamed: CHANNEL1.6 (ADC8), CON6.D24 (D24~T14~IO_L20P_2)
unnamed: CHANNEL1.5 (ADC7), CON6.F24 (F24~U14~IO_L20N_2)
unnamed: CHANNEL1.4 (ADCOR), CON6.C25 (C25~W9~IO_L47P_2)
unnamed: CHANNEL1.3 (ADC9), CON6.D25 (D25~W12~IO_L42P_2)
unnamed: CHANNEL1.2 (TRIGIN), CON6.F25 (F25~Y12~IO_L42N_2)
unnamed: LED1.C, LED7.C, R52.1
unnamed: LED2.C, LED8.C, R53.1
unnamed: LED3.C, LED9.C, R54.1
unnamed: LED4.C, LED10.C, R55.1
unnamed: LED5.C, LED11.C, R56.1
unnamed: LED6.C, LED12.C, R57.1
OA_ADC0: CHANNEL2.24 (ADC0), CON6.D10 (D10~AA22~IO_L63N_1); also elsewhere on the board
OA_ADC1: CHANNEL2.21 (ADC1), CON6.F11 (F11~AB21~IO_L61N_1); also elsewhere on the board
OA_ADC2: CHANNEL2.22 (ADC2), CON6.D11 (D11~Y21~IO_L59P_1); also elsewhere on the board
OA_ADC3: CHANNEL2.19 (ADC3), CON6.F12 (F12~Y20~IO_L67N_1); also elsewhere on the board
OA_ADC4: CHANNEL2.20 (ADC4), CON6.D12 (D12~W20~IO_L53P_1); also elsewhere on the board
OA_ADC5: CHANNEL2.7 (ADC5), CON6.F13 (F13~AB20~IO_L65N_1); also elsewhere on the board
OA_ADC6: CHANNEL2.8 (ADC6), CON6.D13 (D13~AA20~IO_L61P_1); also elsewhere on the board
OA_ADC7: CHANNEL2.5 (ADC7), CON6.F14 (F14~AB19~IO_L65P_1); also elsewhere on the board
OA_ADC8: CHANNEL2.6 (ADC8), CON6.D14 (D14~V19~IO_L71P_1); also elsewhere on the board
OA_ADC9: CHANNEL2.3 (ADC9), CON6.F15 (F15~AB18~IO_L2N_CMPMOSI_2); also elsewhere on the board
OA_ADCOR: CHANNEL2.4 (ADCOR), CON6.D15 (D15~Y19~IO_L67P_1); also elsewhere on the board
OA_CLKADC: CHANNEL2.23 (CLKADC), CON6.F10 (F10~AA21~IO_L63P_1); also elsewhere on the board
OA_CLKIN: CHANNEL2.1 (CLKIN), CON6.C20 (C20~Y11~IO_L31P_GCLK31_D14_2); also elsewhere on the board
OA_GAIN: CHANNEL2.25 (GAIN), CON6.D9 (D9~Y22~IO_L59N_1); also elsewhere on the board
OA_HILO: CHANNEL2.26 (HILO), CON6.D8 (D8~V20~IO_L71N_1); also elsewhere on the board
OA_TRIGIN: CHANNEL2.2 (TRIGIN), CON6.D16 (D16~V18~IO_L73N_1)

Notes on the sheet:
L12
M12
R12
M11
T12
M10
M13
L13
R14
N14
K15
L14
T15
R15
P15
M15
P16
N16
M16
L16
K16
ZTEX 1.11 FPGA
